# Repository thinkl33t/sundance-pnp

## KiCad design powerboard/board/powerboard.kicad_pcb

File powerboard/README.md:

This directory contains the Sundance Power board.

The board is CAD'd out in [Kicad](http://kicad-pcb.org/).

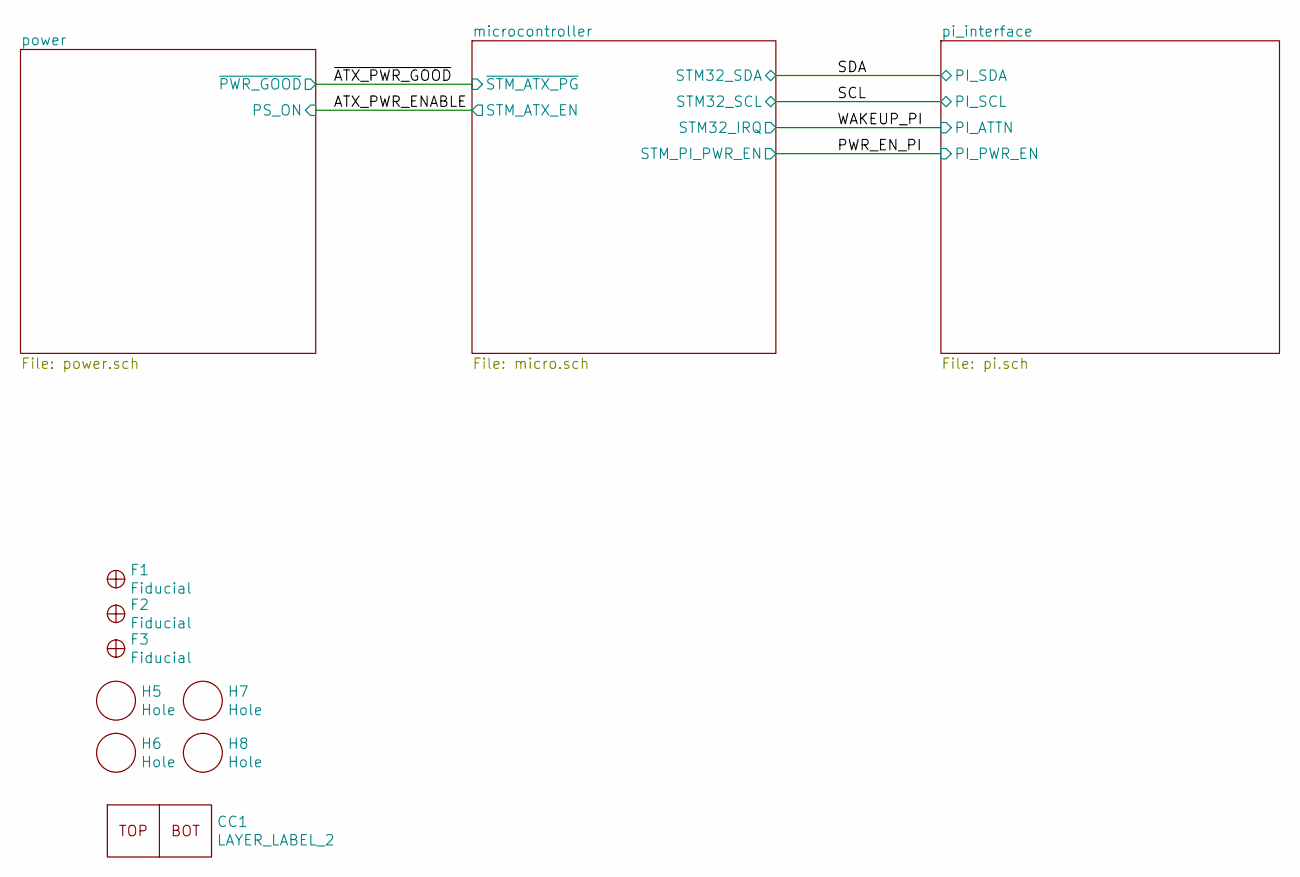
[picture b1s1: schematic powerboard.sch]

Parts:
CC1: LAYER_LABEL_2
F1, F2, F3: Fiducial; Fiducial_1mm_Dia_2.54mm_Outer_CopperTop
H5, H6, H7, H8: Hole; MountingHole_2.7mm_M2.5

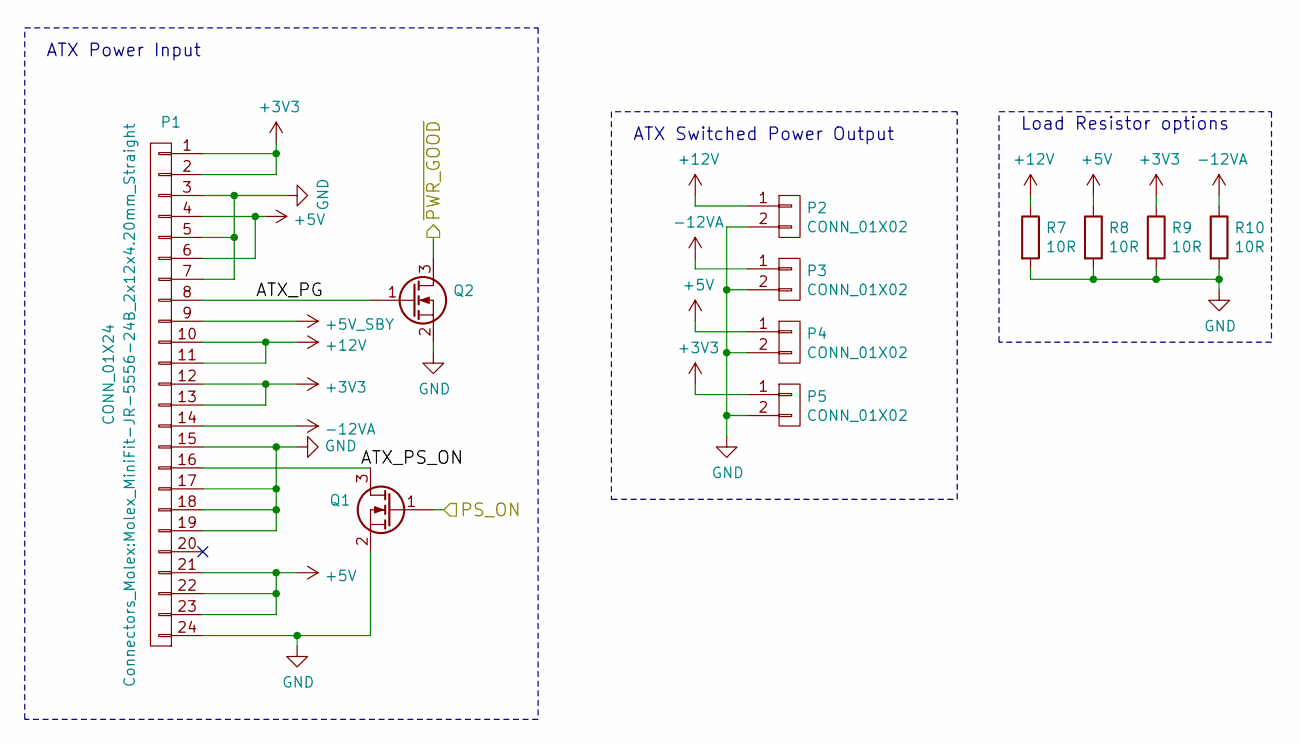
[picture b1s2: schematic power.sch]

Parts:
P1: CONN_01X24; Molex_MiniFit-JR-5556-24B_2x12x4.20mm_Straight
P2, P3, P4, P5: CONN_01X02; TerminalBlock_Pheonix_MKDS1.5-2pol
Q1, Q2: Q_NMOS_GSD; SOT-23
R7, R8, R9, R10: 10R; Resistor_Vertical_RM7.5mm

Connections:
+3V3: P1.1, P1.2, P1.12, P1.13, P5.1, R9.1
+5V: P1.4, P1.6, P1.21, P1.22, P1.23, P4.1, R8.1; also elsewhere on the board
+5V_SBY: P1.9; also elsewhere on the board
+12V: P1.10, P1.11, P2.1, R7.1; also elsewhere on the board
-12VA: P1.14, P3.1, R10.1
/ATX_PWR_ENABLE: Q1.1 (G); also elsewhere on the board
/power/ATX_PG: P1.8, Q2.1 (G)
/power/ATX_PS_ON: P1.16, Q1.3 (D)
/~ATX_PWR_GOOD~: Q2.3 (D); also elsewhere on the board
GND: P1.3, P1.5, P1.7, P1.15, P1.17, P1.18, P1.19, P1.24, P2.2, P3.2, P4.2, P5.2, Q1.2 (S), Q2.2 (S), R7.2, R8.2, R9.2, R10.2; also elsewhere on the board

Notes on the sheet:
ATX Power Input
ATX Switched Power Output
Load Resistor options

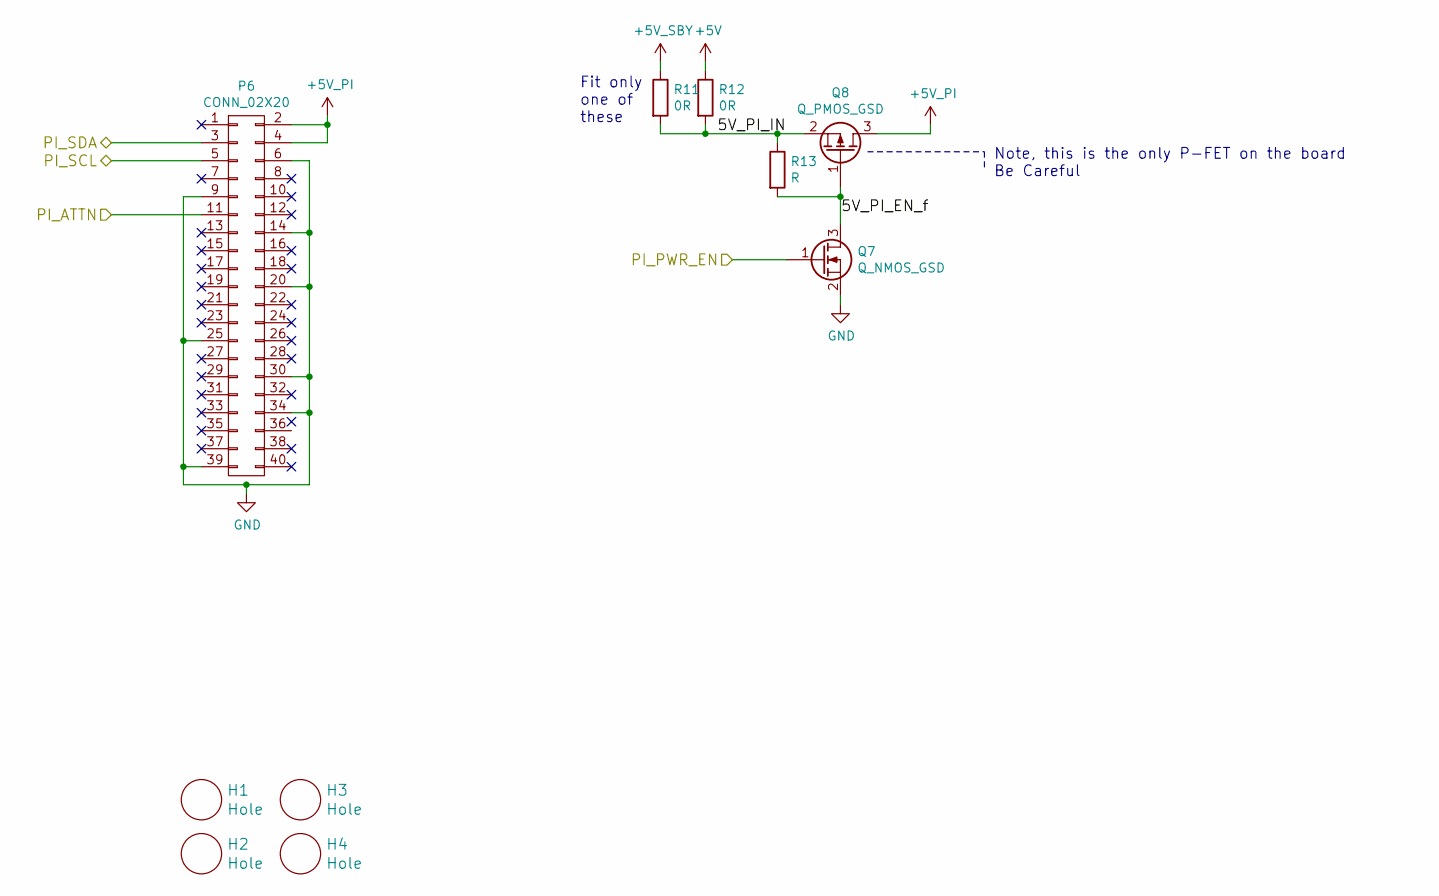
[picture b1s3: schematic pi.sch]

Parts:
H1, H2, H3, H4: Hole; MountingHole_2.7mm_M2.5
P6: CONN_02X20; Pin_Header_Straight_2x20
Q7: Q_NMOS_GSD; SOT-23
Q8: Q_PMOS_GSD; SOT-23
R11, R12: 0R; R_0603_HandSoldering
R13: R; R_0603_HandSoldering

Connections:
+5V: R12.1; also elsewhere on the board
+5V_PI: P6.2, P6.4, Q8.3 (D)
+5V_SBY: R11.1; also elsewhere on the board
/PWR_EN_PI: Q7.1 (G); also elsewhere on the board
/SCL: P6.5; also elsewhere on the board
/SDA: P6.3; also elsewhere on the board
/WAKEUP_PI: P6.11; also elsewhere on the board
/pi_interface/5V_PI_EN_f: Q7.3 (D), Q8.1 (G), R13.2
/pi_interface/5V_PI_IN: Q8.2 (S), R11.2, R12.2, R13.1
GND: P6.6, P6.9, P6.14, P6.20, P6.25, P6.30, P6.34, P6.39, Q7.2 (S); also elsewhere on the board

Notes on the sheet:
Fit only one of these
Note, this is the only P-FET on the board Be Careful

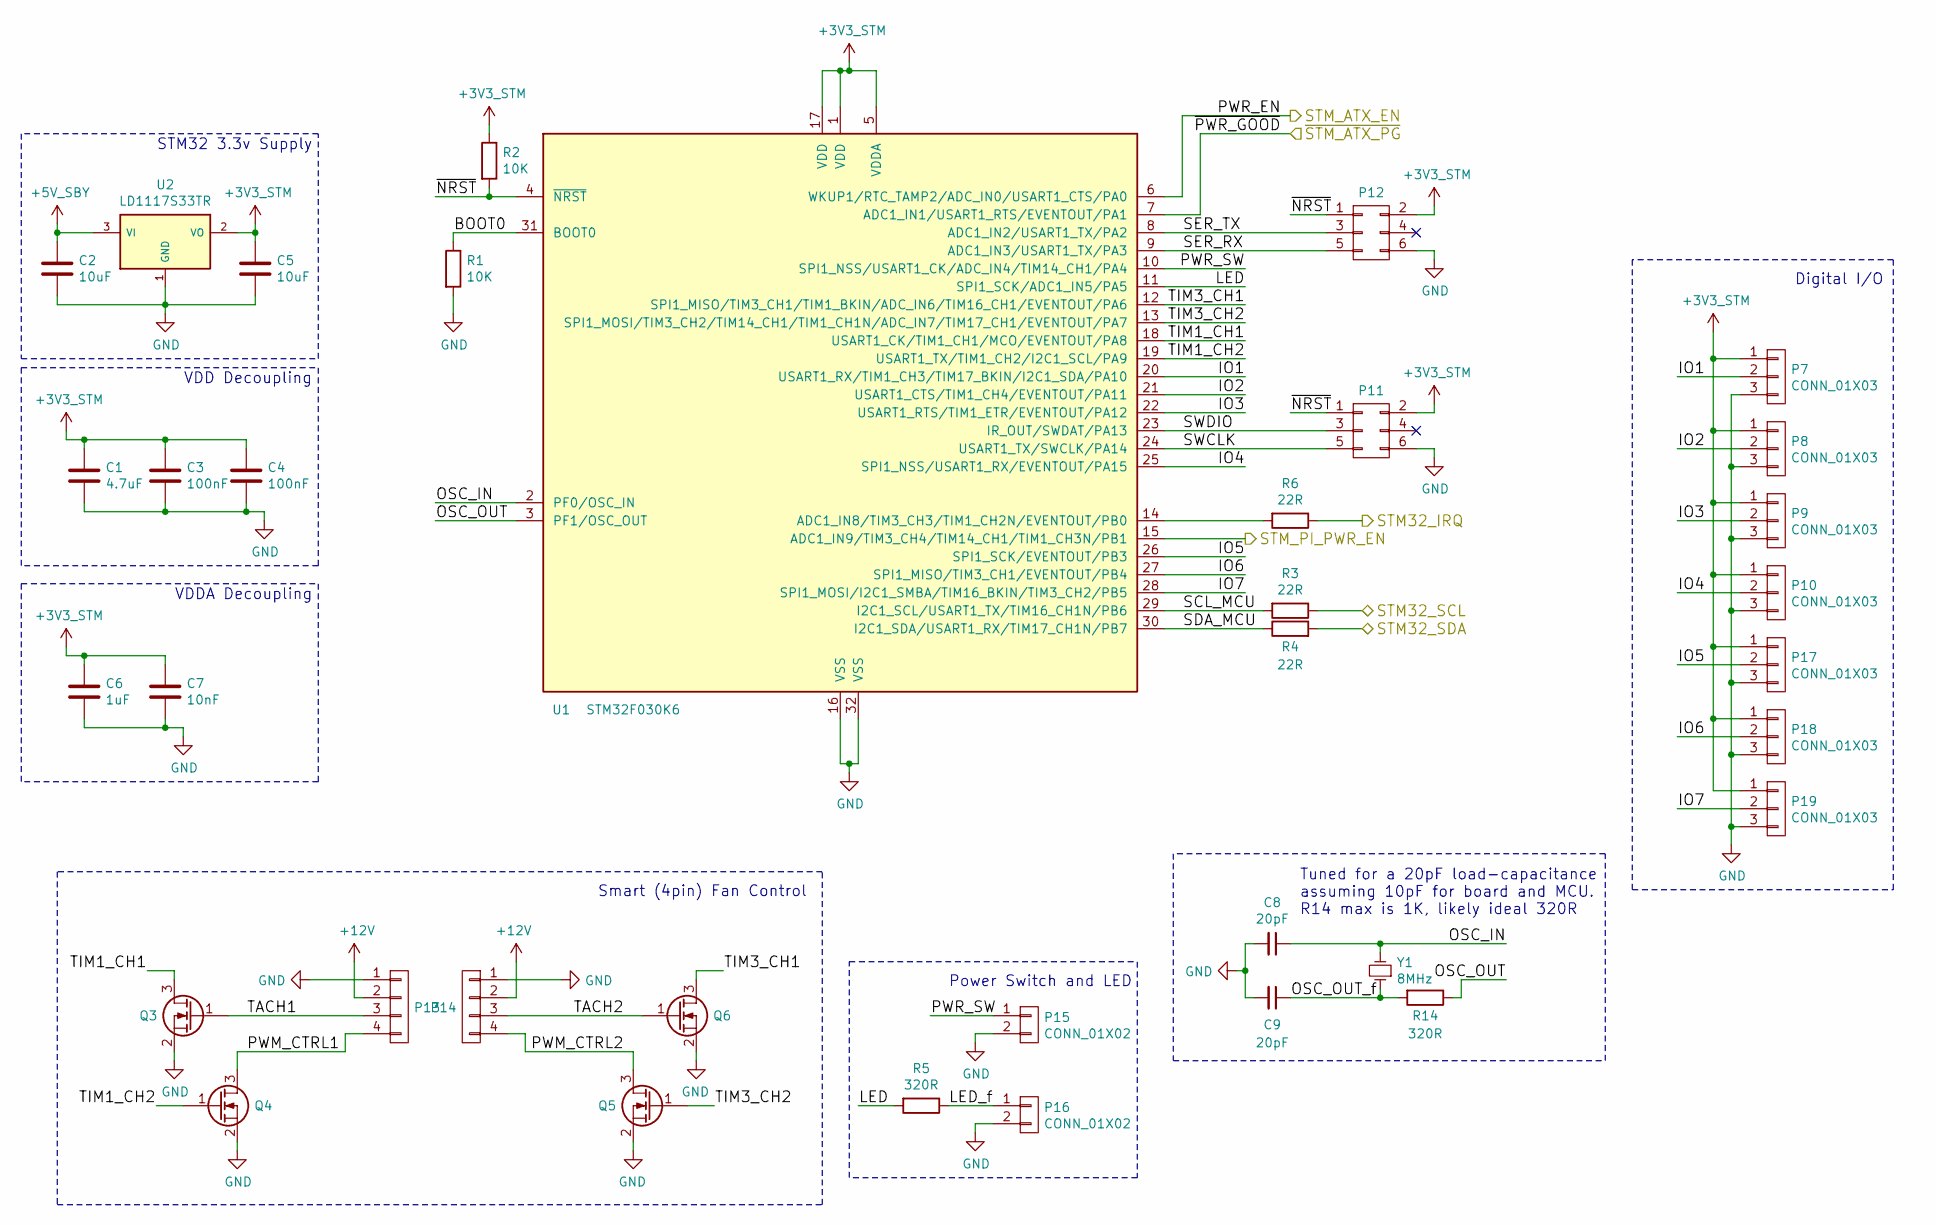
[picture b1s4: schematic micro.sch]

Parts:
C1: 4.7uF; C_0603_HandSoldering
C2, C5: 10uF; C_0603_HandSoldering
C3, C4: 100nF; C_0603_HandSoldering
C6: 1uF; C_0603_HandSoldering
C7: 10nF; C_0603_HandSoldering
C8, C9: 20pF; C_0603_HandSoldering
P7, P8, P9, P10, P17, P18, P19: CONN_01X03; Socket_MOLEX-KK-RM2-54mm_Lock_3pin_straight
P11, P12: CONN_02X03; TC2030-MCP-NL
P13, P14: CONN_01X04; Molex_KK-6410-04_04x2.54mm_Straight
P15, P16: CONN_01X02; Molex_KK-6410-02_02x2.54mm_Straight
Q3, Q4, Q5, Q6: Q_NMOS_GSD; SOT-23
R1, R2: 10K; R_0603_HandSoldering
R3, R4, R6: 22R; R_0603_HandSoldering
R5, R14: 320R; R_0603_HandSoldering
U1: STM32F030K6; LQFP-32_7x7mm_Pitch0.8mm
U2: LD1117S33TR; SOT-223
Y1: 8MHz; Crystal_HC49-SD_SMD

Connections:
+3V3_STM: C1.1, C3.1, C4.1, C5.1, C6.1, C7.1, P7.1, P8.1, P9.1, P10.1, P11.2, P12.2, P17.1, P18.1, P19.1, R2.1, U1.1 (VDD), U1.5 (VDDA), U1.17 (VDD), U2.2 (VO)
+5V_SBY: C2.1, U2.3 (VI); also elsewhere on the board
+12V: P13.2, P14.2; also elsewhere on the board
/ATX_PWR_ENABLE: U1.6 (WKUP1/RTC_TAMP2/ADC_IN0/USART1_CTS/PA0); also elsewhere on the board
/PWR_EN_PI: U1.15 (ADC1_IN9/TIM3_CH4/TIM14_CH1/TIM1_CH3N/P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); also elsewhere on the board
/SCL: R3.1; also elsewhere on the board
/SDA: R4.2; also elsewhere on the board
/WAKEUP_PI: R6.1; also elsewhere on the board
/microcontroller/BOOT0: R1.1, U1.31 (BOOT0)
/microcontroller/IO1: P7.2, U1.20 (USART1_RX/TIM1_CH3/TIM17_BKIN/I2C1_SDA/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)
/microcontroller/IO2: P8.2, U1.21 (USART1_CTS/TIM1_CH4/EVENTOUT/PA11)
/microcontroller/IO3: P9.2, U1.22 (USART1_RTS/TIM1_ETR/EVENTOUT/PA12)
/microcontroller/IO4: P10.2, U1.25 (SPI1_NSS/USART1_RX/EVENTOUT/PA15)
/microcontroller/IO5: P17.2, U1.26 (SPI1_SCK/EVENTOUT/PB3)
/microcontroller/IO6: P18.2, U1.27 (SPI1_MISO/TIM3_CH1/EVENTOUT/PB4)
/microcontroller/IO7: P19.2, U1.28 (SPI1_MOSI/I2C1_SMBA/TIM16_BKIN/TIM3_CH2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)
/microcontroller/LED: R5.2, U1.11 (SPI1_SCK/ADC1_IN5/PA5)
/microcontroller/LED_f: P16.1, R5.1
/microcontroller/OSC_IN: C8.1, U1.2 (PF0/OSC_IN), Y1.2
/microcontroller/OSC_OUT: R14.1, U1.3 (PF1/OSC_OUT)
/microcontroller/OSC_OUT_f: C9.1, R14.2, Y1.1
/microcontroller/PWM_CTRL1: P13.4, Q4.3 (D)
/microcontroller/PWM_CTRL2: P14.4, Q5.3 (D)
/microcontroller/PWR_SW: P15.1, U1.10 (SPI1_NSS/USART1_CK/ADC_IN4/TIM14_CH1/PA4)
/microcontroller/SCL_MCU: R3.2, U1.29 (I2C1_SCL/USART1_TX/TIM16_CH1N/PB6)
/microcontroller/SDA_MCU: R4.1, U1.30 (I2C1_SDA/USART1_RX/TIM17_CH1N/PB7)
/microcontroller/SER_RX: P12.5, U1.9 (ADC1_IN3/USART1_TX/PA3)
/microcontroller/SER_TX: P12.3, U1.8 (ADC1_IN2/USART1_TX/PA2)
/microcontroller/SWCLK: P11.5, U1.24 (USART1_TX/SWCLK/PA14)
/microcontroller/SWDIO: P11.3, U1.23 (IR_OUT/SWDAT/PA13)
/microcontroller/TACH1: P13.3, Q3.1 (G)
/microcontroller/TACH2: P14.3, Q6.1 (G)
/microcontroller/TIM1_CH1: Q3.3 (D), U1.18 (USART1_CK/TIM1_CH1/MCO/EVENTOUT/PA8)
/microcontroller/TIM1_CH2: Q4.1 (G), U1.19 (USART1_TX/TIM1_CH2/I2C1_SCL/PA9)
/microcontroller/TIM3_CH1: Q6.3 (D), U1.12 (SPI1_MISO/TIM3_CH1/TIM1_BKIN/ADC_IN6/TI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)
/microcontroller/TIM3_CH2: Q5.1 (G), U1.13 (SPI1_MOSI/TIM3_CH2/TIM14_CH1/TIM1_CH1N/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)
/microcontroller/~NRST~: P11.1, P12.1, R2.2, U1.4 (~NRST)
/~ATX_PWR_GOOD~: U1.7 (ADC1_IN1/USART1_RTS/EVENTOUT/PA1); also elsewhere on the board
GND: C1.2, C2.2, C3.2, C4.2, C5.2, C6.2, C7.2, C8.2, C9.2, P7.3, P8.3, P9.3, P10.3, P11.6, P12.6, P13.1, P14.1, P15.2, P16.2, P17.3, P18.3, P19.3, Q3.2 (S), Q4.2 (S), Q5.2 (S), Q6.2 (S), R1.2, U1.16 (VSS), U1.32 (VSS), U2.1 (GND); also elsewhere on the board
unnamed: R6.2, U1.14 (ADC1_IN8/TIM3_CH3/TIM1_CH2N/EVENTOUT/PB0)

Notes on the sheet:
VDD Decoupling
VDDA Decoupling
STM32 3.3v Supply
Smart (4pin) Fan Control
Power Switch and LED
Digital I/O
Tuned for a 20pF load-capacitance assuming 10pF for board and MCU. R14 max is 1K, likely ideal 320R

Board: 2 copper layers, 65 parts (2 on the bottom side), 48 nets, no tracks yet.

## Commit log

2016-08-20 Initial Project Notes
2016-12-24 Updated project Notes
2016-12-24 Added CAD files and CAM output files
2016-12-27 Initial commit of powerboard project and library.

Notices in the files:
powerboard/board/powerboard.kicad_pcb:
Sundance Power Board ©2016/2017 Daniel Silverstone and Bob Clough
